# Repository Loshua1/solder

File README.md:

# Solder

Slack Username: Loshua1

## BOM
- 1 Battery Cell (BatteryHolder_Keystone_3034_1x20mm)
- 2 LEDs (LED_D5.0mm)
- 2 Resistors (R_Axial_DIN0207_L6.3mm_D2.5mm_P7.62mm_Horizontal)

## Schematic

## PCB

## 3D View

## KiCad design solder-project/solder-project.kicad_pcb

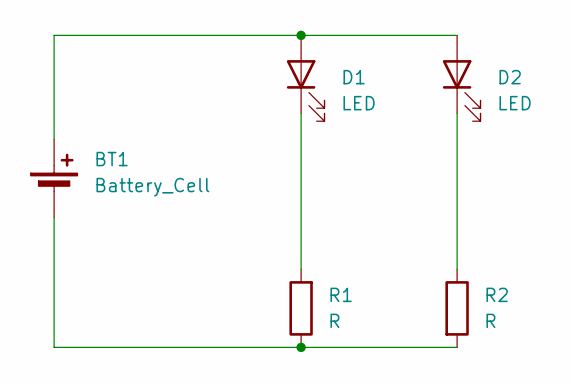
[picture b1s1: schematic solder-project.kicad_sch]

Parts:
BT1: Battery_Cell; BatteryHolder_Keystone_3034_1x20mm
D1, D2: LED; LED_D5.0mm
R1, R2: R; R_Axial_DIN0207_L6.3mm_D2.5mm_P7.62mm_Horizontal

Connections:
unnamed: BT1.1 (+), D1.2 (A), D2.2 (A)
unnamed: BT1.2 (-), R1.1, R2.2
unnamed: D1.1 (K), R1.2
unnamed: D2.1 (K), R2.1

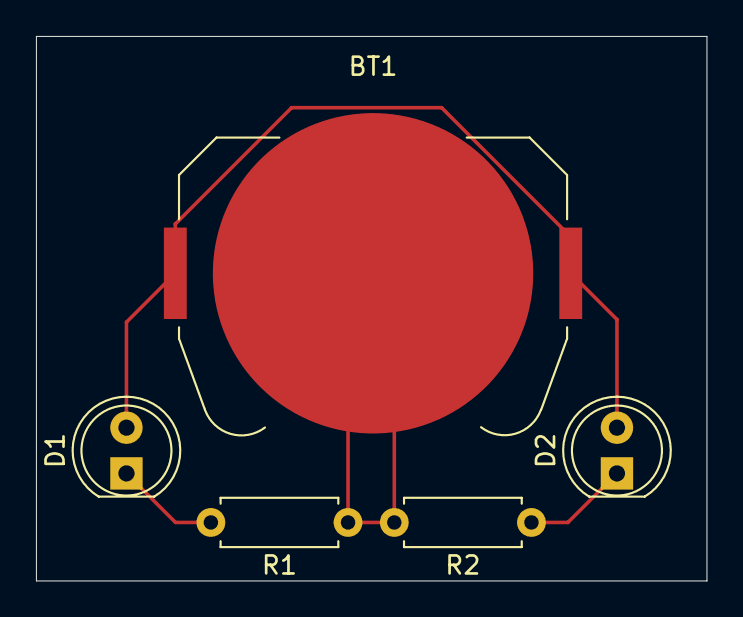
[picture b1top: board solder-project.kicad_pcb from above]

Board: 2 copper layers, 37.2 x 30.2 mm, 5 parts (0 on the bottom side), 4 nets.
